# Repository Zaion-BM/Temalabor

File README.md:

# Témalabor
University project at BME-VIK-MIT

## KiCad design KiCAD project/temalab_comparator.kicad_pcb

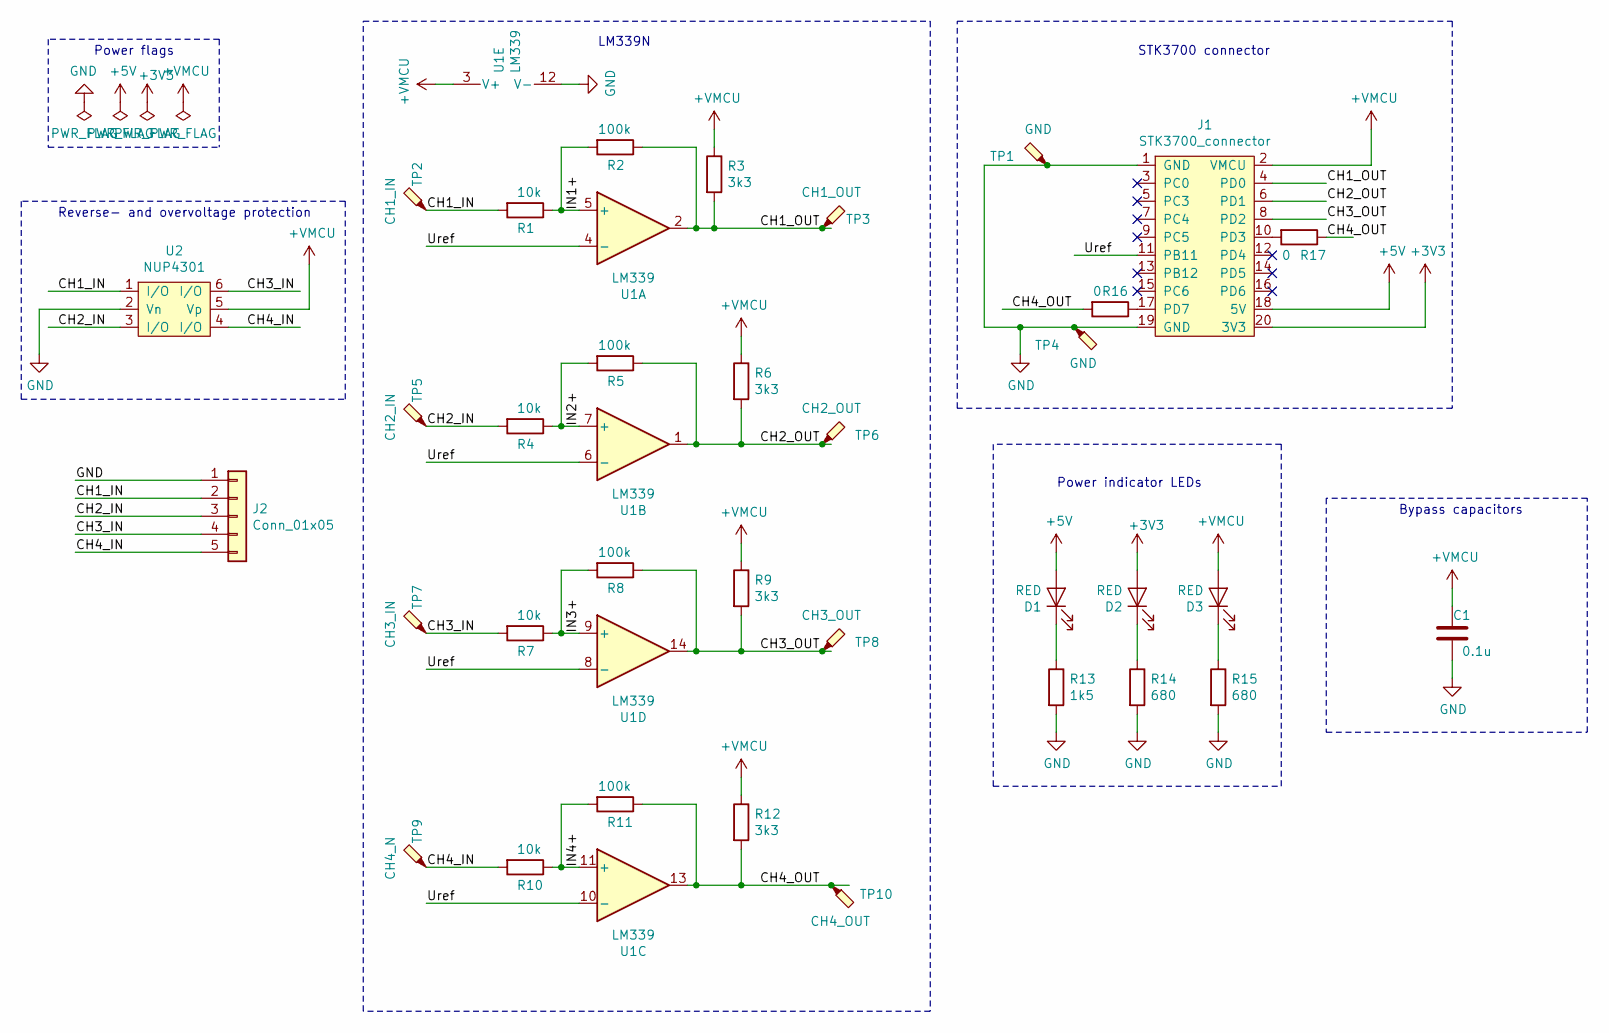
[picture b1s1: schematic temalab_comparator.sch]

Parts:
C1: 0.1u; C_0805_2012Metric_Pad1.15x1.40mm_HandSolder
D1, D2, D3: RED; LED_0805_2012Metric_Pad1.15x1.40mm_HandSolder
J1: STK3700_connector; PinSocket_2x10_P2.54mm_Horizontal_STK3700
J2: Conn_01x05; PinSocket_1x05_P2.54mm_Vertical
R1, R4, R7, R10: 10k; R_0805_2012Metric_Pad1.15x1.40mm_HandSolder
R2, R5, R8, R11: 100k; R_0805_2012Metric_Pad1.15x1.40mm_HandSolder
R3, R6, R9, R12: 3k3; R_0805_2012Metric_Pad1.15x1.40mm_HandSolder
R13: 1k5; R_0805_2012Metric_Pad1.15x1.40mm_HandSolder
R14, R15: 680; R_0805_2012Metric_Pad1.15x1.40mm_HandSolder
R16, R17: 0; R_0805_2012Metric_Pad1.15x1.40mm_HandSolder
TP1, TP4: GND; TestPoint_THTPad_D1.5mm_Drill0.7mm_Value_on_Silk_Screen
TP2: CH1_IN; TestPoint_THTPad_D1.5mm_Drill0.7mm_Value_on_Silk_Screen
TP3: CH1_OUT; TestPoint_THTPad_D1.5mm_Drill0.7mm_Value_on_Silk_Screen
TP5: CH2_IN; TestPoint_THTPad_D1.5mm_Drill0.7mm_Value_on_Silk_Screen
TP6: CH2_OUT; TestPoint_THTPad_D1.5mm_Drill0.7mm_Value_on_Silk_Screen
TP7: CH3_IN; TestPoint_THTPad_D1.5mm_Drill0.7mm_Value_on_Silk_Screen
TP8: CH3_OUT; TestPoint_THTPad_D1.5mm_Drill0.7mm_Value_on_Silk_Screen
TP9: CH4_N; TestPoint_THTPad_D1.5mm_Drill0.7mm_Value_on_Silk_Screen
TP10: CH4_OUT; TestPoint_THTPad_D1.5mm_Drill0.7mm_Value_on_Silk_Screen
U1: LM339; DIP-14_W7.62mm_LM339n
U2: NUP4301; TSOP-6_1.65x3.05mm_P0.95mm_NUP4301

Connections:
+3V3: D2.2 (A), J1.20 (3V3)
+5V: D1.2 (A), J1.18 (5V)
/CH1_IN: J2.2, R1.2, TP2.1, U2.1 (I/O)
/CH1_OUT: J1.4 (PD0), R2.1, R3.2, TP3.1, U1.2
/CH2_IN: J2.3, R4.2, TP5.1, U2.3 (I/O)
/CH2_OUT: J1.6 (PD1), R5.1, R6.2, TP6.1, U1.1
/CH3_IN: J2.4, R7.2, TP7.1, U2.6 (I/O)
/CH3_OUT: J1.8 (PD2), R8.1, R9.2, TP8.1, U1.14
/CH4_IN: J2.5, R10.2, TP9.1, U2.4 (I/O)
/CH4_OUT: R11.1, R12.2, R16.2, R17.1, TP10.1, U1.13
/IN1+: R1.1, R2.2, U1.5 (+)
/IN2+: R4.1, R5.2, U1.7 (+)
/IN3+: R7.1, R8.2, U1.9 (+)
/IN4+: R10.1, R11.2, U1.11 (+)
/Uref: J1.11 (PB11), U1.4 (-), U1.6 (-), U1.8 (-), U1.10 (-)
GND: C1.1, J1.1 (GND), J1.19 (GND), J2.1, R13.2, R14.2, R15.2, TP1.1, TP4.1, U1.12 (V-), U2.2 (Vn)
unnamed: D1.1 (K), R13.1
unnamed: D2.1 (K), R14.1
unnamed: D3.1 (K), R15.1
unnamed: J1.10 (PD3), R17.2
unnamed: J1.17 (PD7), R16.1
VMCU: C1.2, D3.2 (A), J1.2 (VMCU), R3.1, R6.1, R9.1, R12.1, U1.3 (V+), U2.5 (Vp)

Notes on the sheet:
STK3700 connector
Power indicator LEDs
Power flags
Bypass capacitors
Reverse- and overvoltage protection
LM339N

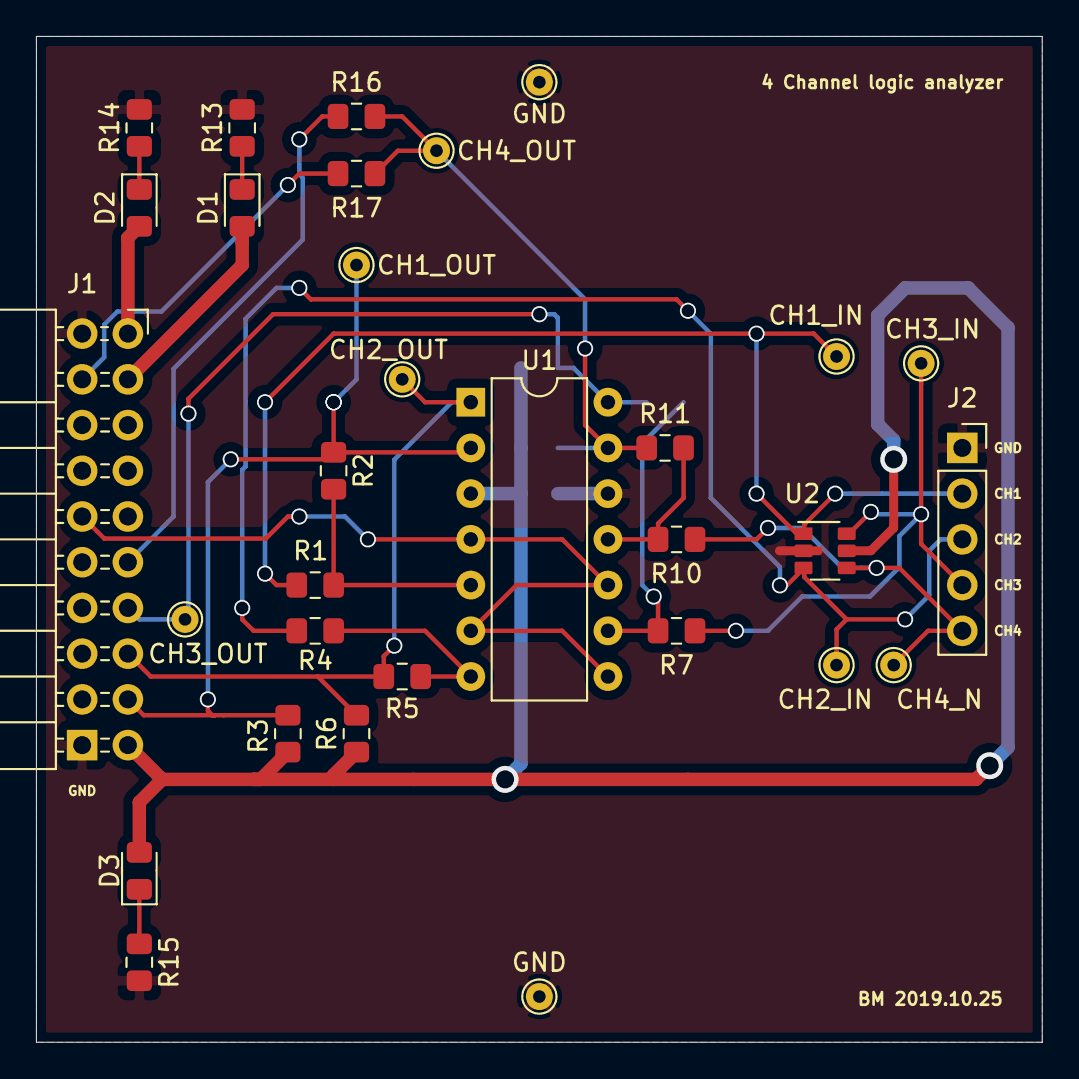
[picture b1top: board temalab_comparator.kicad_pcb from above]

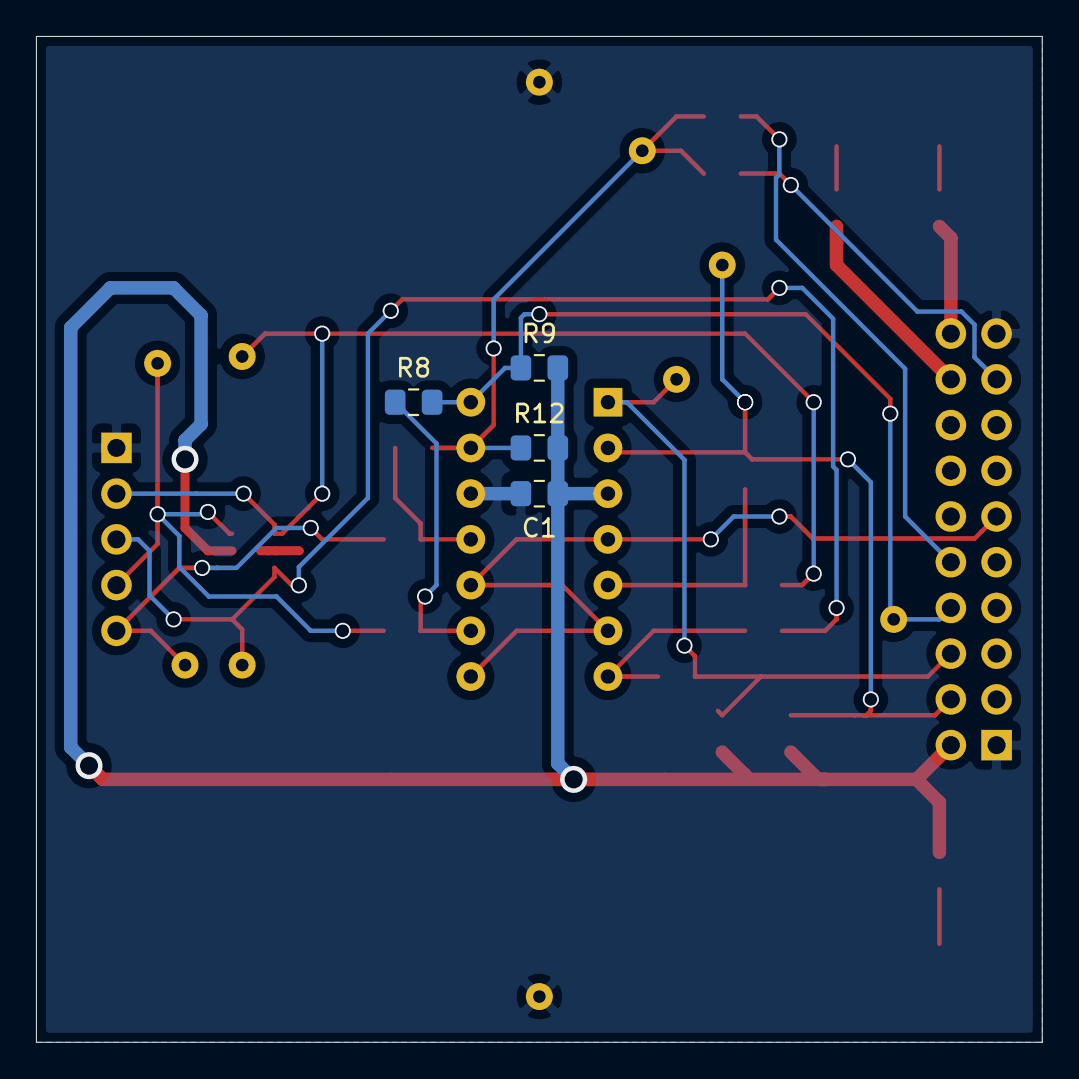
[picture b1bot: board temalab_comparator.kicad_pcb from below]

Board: 2 copper layers, 55.9 x 55.9 mm, 35 parts (4 on the bottom side), 22 nets.

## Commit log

2020-12-06 Schematic & PCB project
    Went to production
2020-12-06 Schematic & PCB
    Went to production
2020-12-06 Firmware
    Made for STK3700 development kit
2020-12-06 Documentation
2021-03-04 Presetation added.
